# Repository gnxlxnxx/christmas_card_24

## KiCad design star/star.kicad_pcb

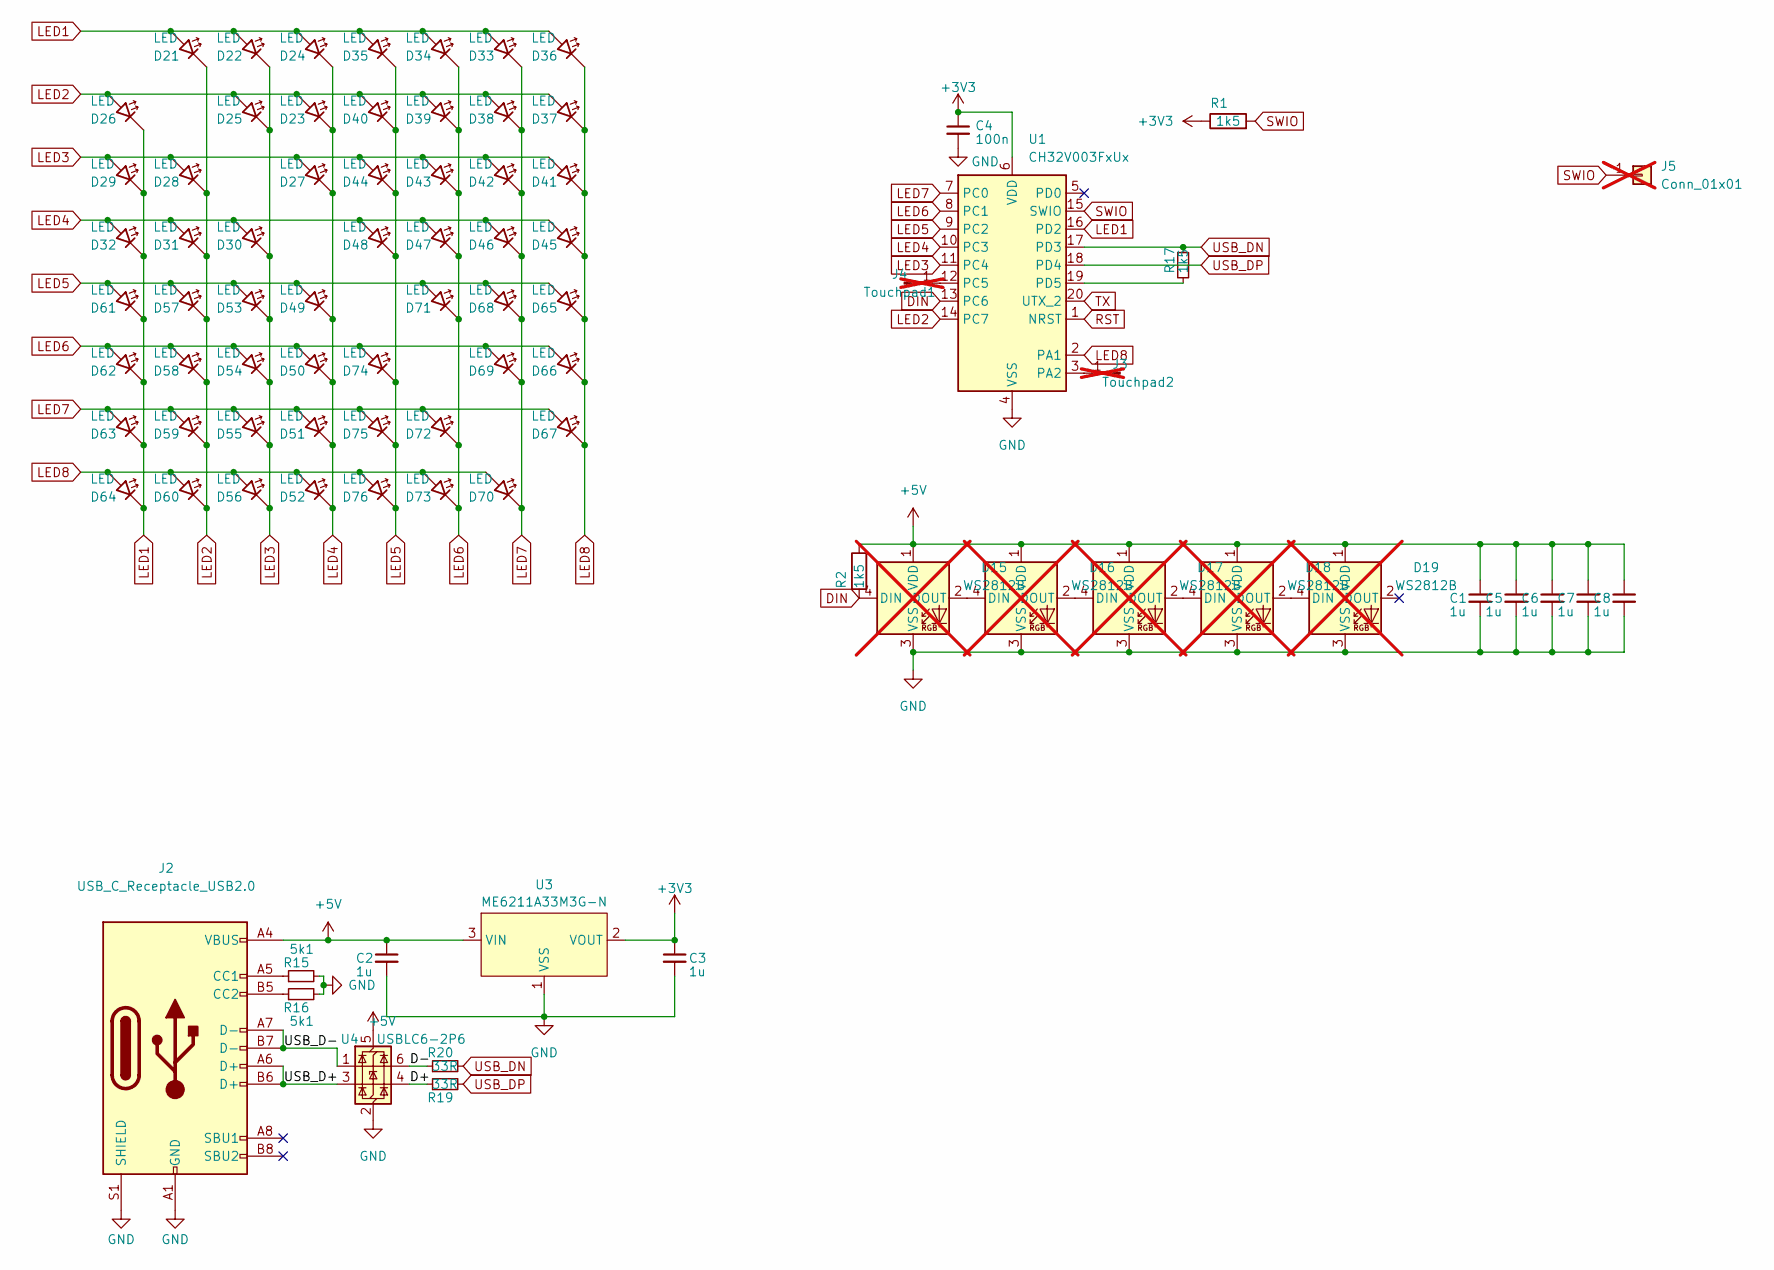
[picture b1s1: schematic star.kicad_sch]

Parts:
C1, C2, C3, C5, C6, C7, C8: 1u; C_0402_1005Metric; LCSC C52923
C4: 100n; C_0402_1005Metric; LCSC C1525
D15, D16, D17, D18, D19: WS2812B; LED_WS2812B_PLCC4_5.0x5.0mm_P3.2mm; LCSC C965555; not fitted
D21, D22, D23, D24, D25, D26, D27, D28, D29, D30, D31, D32, D33, D34, D35, D36, D37, D38, D39, D40, D41, D42, D43, D44, D45, D46, D47, D48, D49, D50, D51, D52, D53, D54, D55, D56, D57, D58, D59, D60, D61, D62, D63, D64, D65, D66, D67, D68, D69, D70, D71, D72, D73, D74, D75, D76: LED; LED_0603_1608Metric_Pad1.05x0.95mm_HandSolder; LCSC C497938
J2: USB_C_Receptacle_USB2.0; TYPE C 16 PIN MIDDLE MOUNT CH 0.52; LCSC C2927036
J3: Touchpad2; touch_pad; not fitted
J4: Touchpad1; touch_pad; not fitted
J5: Conn_01x01; pogo_pin_conn_01x01; not fitted
R1, R2, R17: 1k5; R_0402_1005Metric; LCSC C25867
R15, R16: 5k1; R_0402_1005Metric; LCSC C25905
R19, R20: 33R; R_0402_1005Metric; LCSC C25105
U1: CH32V003FxUx; QFN-20-1EP_3x3mm_P0.4mm_EP1.65x1.65mm; LCSC C5299908
U3: ME6211A33M3G-N; SOT-23-3; LCSC C168807
U4: USBLC6-2P6; SOT-666; LCSC C2827693

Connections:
+3V3: C3.1, C4.1, R1.1, U1.6 (VDD), U3.2 (VOUT)
+5V: C1.1, C2.1, C5.1, C6.1, C7.1, C8.1, D15.1 (VDD), D16.1 (VDD), D17.1 (VDD), D18.1 (VDD), D19.1 (VDD), J2.A4 (VBUS), J2.A9 (VBUS), J2.B4 (VBUS), J2.B9 (VBUS), R2.1, U3.3 (VIN), U4.5 (VBUS)
/D+: R19.1, U4.4 (I/O2)
/D-: R20.1, U4.6 (I/O1)
/USB_D+: J2.A6 (D+), J2.B6 (D+), U4.3 (I/O2)
/USB_D-: J2.A7 (D-), J2.B7 (D-), U4.1 (I/O1)
DIN: D15.4 (DIN), R2.2, U1.13 (PC6)
GND: C1.2, C2.2, C3.2, C4.2, C5.2, C6.2, C7.2, C8.2, D15.3 (VSS), D16.3 (VSS), D17.3 (VSS), D18.3 (VSS), D19.3 (VSS), J2.A1 (GND), J2.A12 (GND), J2.B1 (GND), J2.B12 (GND), J2.S1 (SHIELD), R15.2, R16.2, U1.4 (VSS), U1.21 (VSS), U3.1 (VSS), U4.2 (GND)
LED1: D21.2 (A), D22.2 (A), D24.2 (A), D26.1 (K), D29.1 (K), D32.1 (K), D33.2 (A), D34.2 (A), D35.2 (A), D36.2 (A), D61.1 (K), D62.1 (K), D63.1 (K), D64.1 (K), U1.16 (PD2)
LED2: D21.1 (K), D23.2 (A), D25.2 (A), D26.2 (A), D28.1 (K), D31.1 (K), D37.2 (A), D38.2 (A), D39.2 (A), D40.2 (A), D57.1 (K), D58.1 (K), D59.1 (K), D60.1 (K), U1.14 (PC7)
LED3: D22.1 (K), D25.1 (K), D27.2 (A), D28.2 (A), D29.2 (A), D30.1 (K), D41.2 (A), D42.2 (A), D43.2 (A), D44.2 (A), D53.1 (K), D54.1 (K), D55.1 (K), D56.1 (K), U1.11 (PC4)
LED4: D23.1 (K), D24.1 (K), D27.1 (K), D30.2 (A), D31.2 (A), D32.2 (A), D45.2 (A), D46.2 (A), D47.2 (A), D48.2 (A), D49.1 (K), D50.1 (K), D51.1 (K), D52.1 (K), U1.10 (PC3)
LED5: D35.1 (K), D40.1 (K), D44.1 (K), D48.1 (K), D49.2 (A), D53.2 (A), D57.2 (A), D61.2 (A), D65.2 (A), D68.2 (A), D71.2 (A), D74.1 (K), D75.1 (K), D76.1 (K), U1.9 (PC2)
LED6: D34.1 (K), D39.1 (K), D43.1 (K), D47.1 (K), D50.2 (A), D54.2 (A), D58.2 (A), D62.2 (A), D66.2 (A), D69.2 (A), D71.1 (K), D72.1 (K), D73.1 (K), D74.2 (A), U1.8 (PC1)
LED7: D33.1 (K), D38.1 (K), D42.1 (K), D46.1 (K), D51.2 (A), D55.2 (A), D59.2 (A), D63.2 (A), D67.2 (A), D68.1 (K), D69.1 (K), D70.1 (K), D72.2 (A), D75.2 (A), U1.7 (PC0)
LED8: D36.1 (K), D37.1 (K), D41.1 (K), D45.1 (K), D52.2 (A), D56.2 (A), D60.2 (A), D64.2 (A), D65.1 (K), D66.1 (K), D67.1 (K), D70.2 (A), D73.2 (A), D76.2 (A), U1.2 (PA1)
unnamed: D15.2 (DOUT), D16.4 (DIN)
unnamed: D16.2 (DOUT), D17.4 (DIN)
unnamed: D17.2 (DOUT), D18.4 (DIN)
unnamed: D18.2 (DOUT), D19.4 (DIN)
unnamed: J2.A5 (CC1), R15.1
unnamed: J2.B5 (CC2), R16.1
unnamed: J3.1, U1.3 (PA2)
unnamed: J4.1, U1.12 (PC5)
unnamed: R17.2, U1.19 (PD5)
RST: U1.1 (NRST)
SWIO: J5.1, R1.2, U1.15 (SWIO)
TX: U1.20 (UTX_2)
USB_DN: R17.1, R20.2, U1.17 (PD3)
USB_DP: R19.2, U1.18 (PD4)

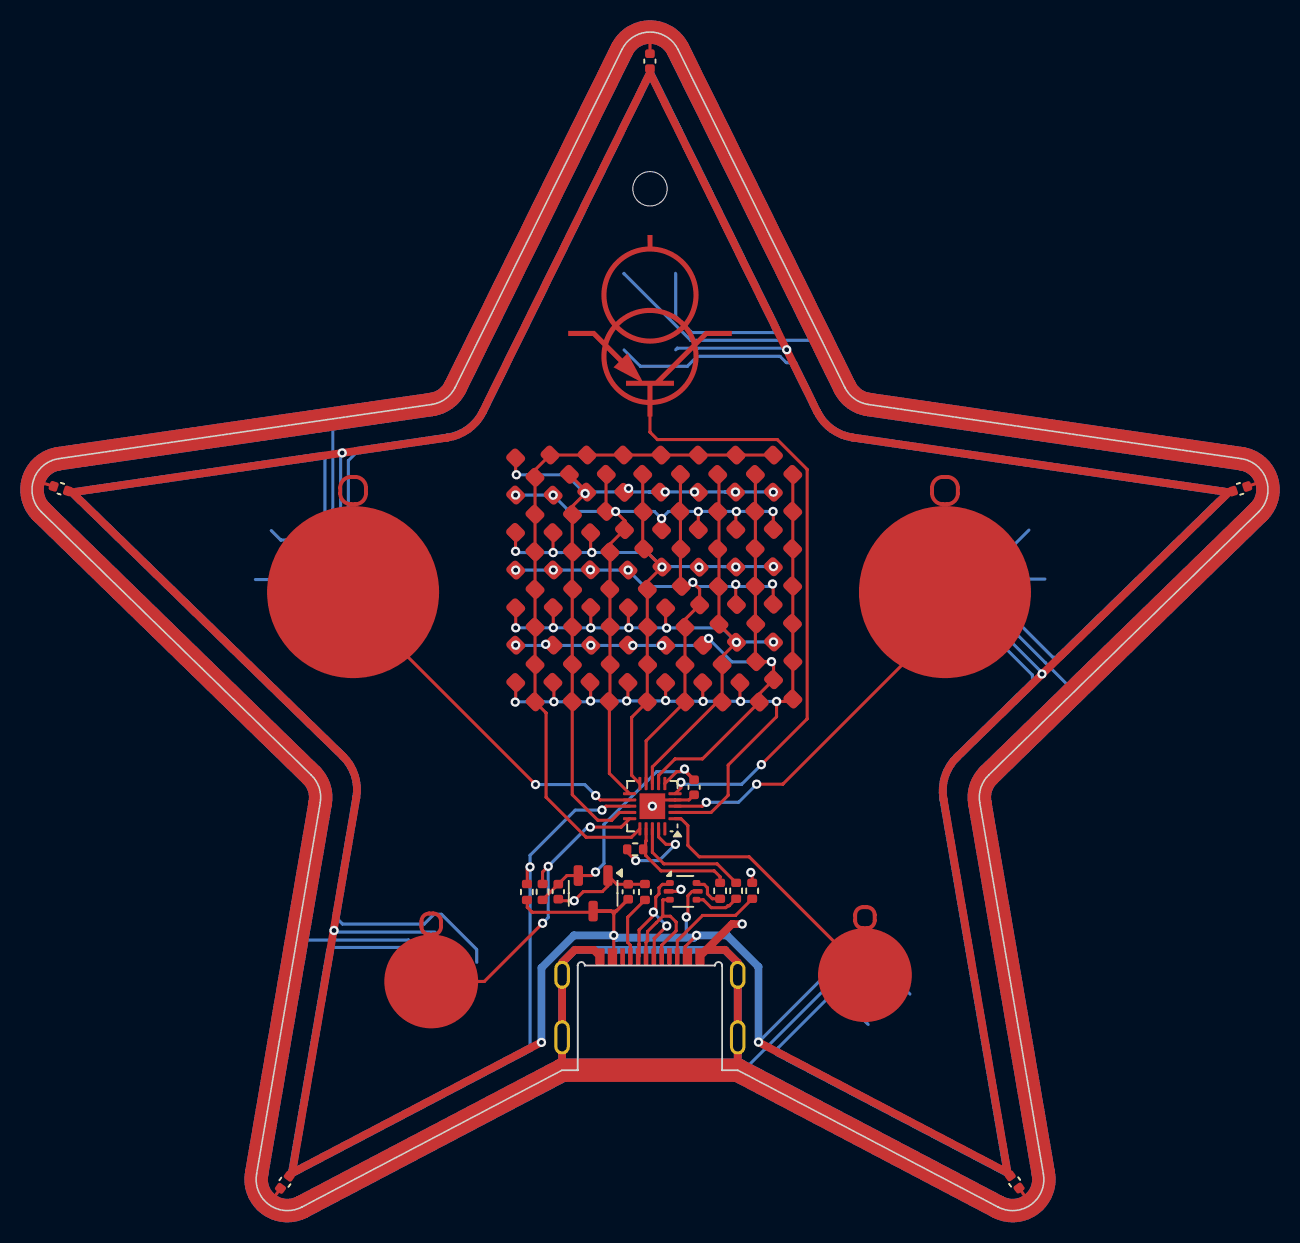
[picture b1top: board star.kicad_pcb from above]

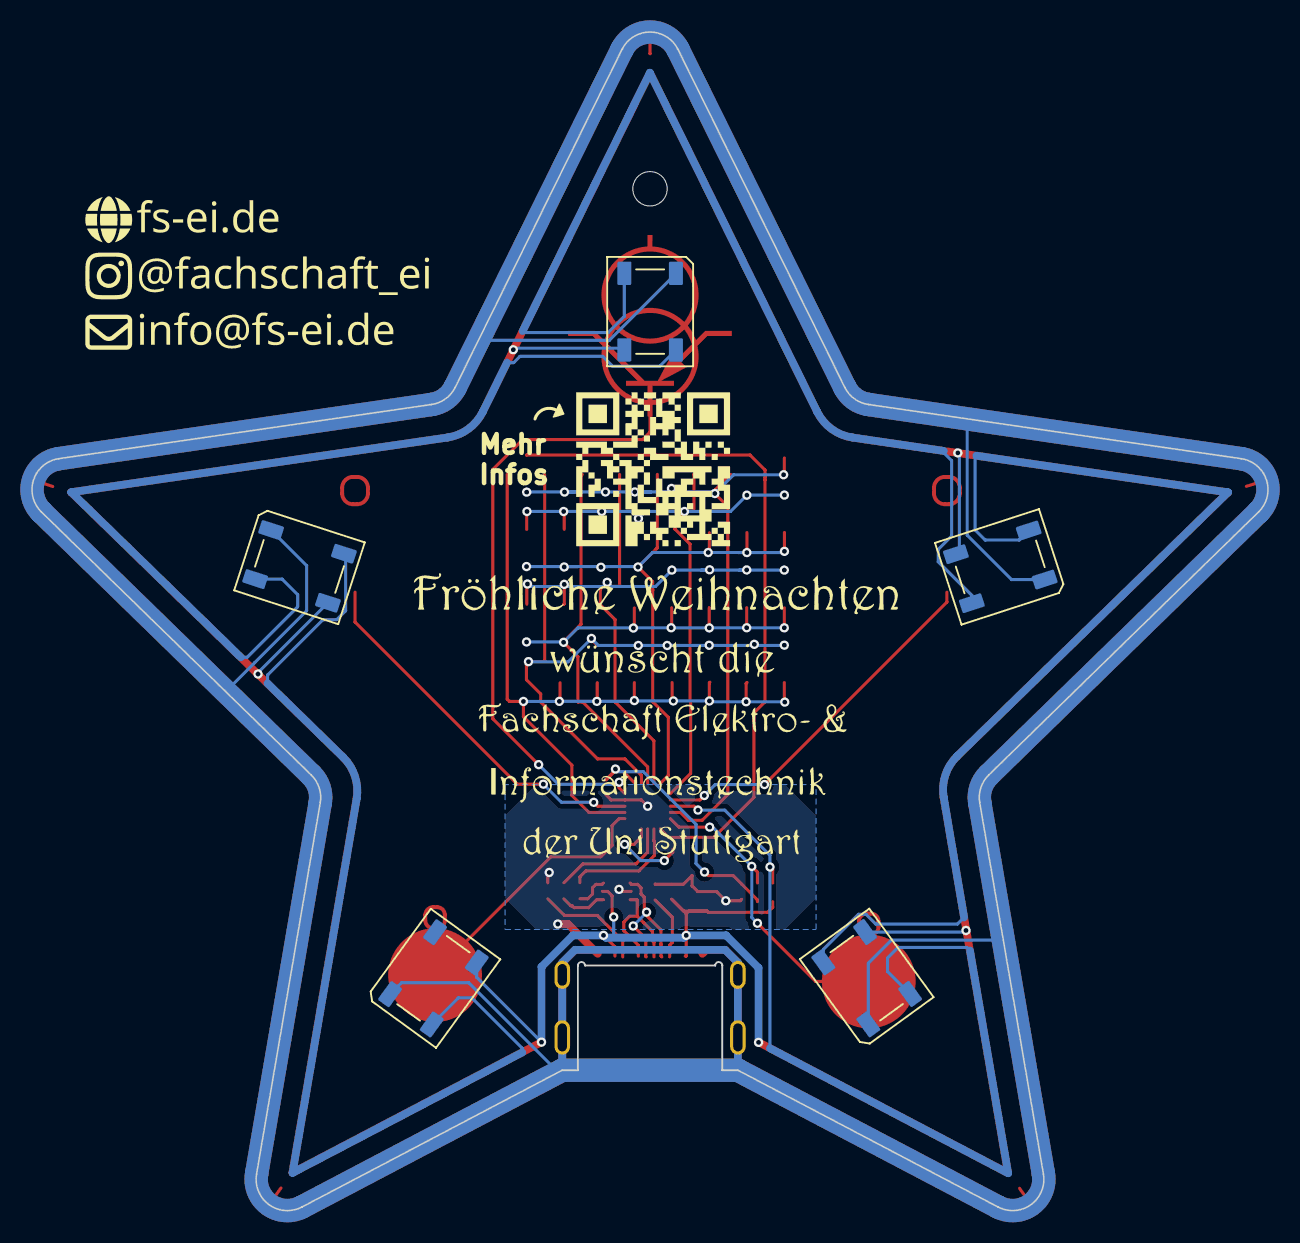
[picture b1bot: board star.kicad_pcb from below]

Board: 2 copper layers, 79.1 x 75.4 mm, 82 parts (5 on the bottom side), 28 nets.

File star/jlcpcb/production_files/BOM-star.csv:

Comment,Designator,Footprint,LCSC,Quantity
100n,C4,C_0402_1005Metric,C1525,1
ME6211A33M3G-N,U3,SOT-23-3,C168807,1
33R,"R19,R20",R_0402_1005Metric,C25105,2
1k5,"R1,R17,R2",R_0402_1005Metric,C25867,3
5k1,"R15,R16",R_0402_1005Metric,C25905,2
USBLC6-2P6,U4,SOT-666,C2827693,1
USB_C_Receptacle_USB2.0,J2,TYPE C 16 PIN MIDDLE MOUNT CH 0.52,C2927036,1
LED,"D21,D22,D23,D24,D25,D26,D27,D28,D29,D30,D31,D32,D33,D34,D35,D36,D37,D38,D39,D40,D41,D42,D43,D44,D45,D46,D47,D48,D49,D50,D51,D52,D53,D54,D55,D56,D57,D58,D59,D60,D61,D62,D63,D64,D65,D66,D67,D68,D69,D70,D71,D72,D73,D74,D75,D76",LED_0603_1608Metric_Pad1.05x0.95mm_HandSolder,C497938,56
1u,"C1,C2,C3,C5,C6,C7,C8",C_0402_1005Metric,C52923,7
CH32V003FxUx,U1,QFN-20-1EP_3x3mm_P0.4mm_EP1.65x1.65mm,C5299908,1
WS2812B,"D16,D18",LED_WS2812B_PLCC4_5.0x5.0mm_P3.2mm,C965555,2

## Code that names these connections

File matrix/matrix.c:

#include <ch32fun.h>
#include <stdint.h>
#include "matrix.h"

#include "gamma_lut.h"

/// LED1:   PD2 *
/// LED2:   PC7 *
/// LED3:   PC4 *
/// LED4:   PC3 *
/// LED5:   PC2 *
/// LED6:   PC1 *
/// LED7:   PC0 *
/// LED8:   PA1 *
///
/// TIM2:
/// 00:     PD4  PD3  PC0  PD7
/// 01:     PC5  PC2* PD2* PC1* *
/// 10:     PC1  PD3  PC0  PD7 
/// 11:     PC1  PC7  PD6  PD5 
///
/// TIM1:
/// 00:     PD2 /PD0  PA1*/PA2  PC3*/PD1  PC4* *
/// 01:     PC6 /PC3  PC7*/PC4  PC0*/PD1  PD3  *
/// 11:     PC4 /PC3  PC7 /PD2  PC5 /PC6  PD4


#define PWM_MAX 4096

#define ROWCOUNT (MATRIX_WIDTH)
#define GROUPCOUNT 2

#define G0T0C2_COL 1
#define G0T0C3_COL 6
#define G0T1C2_COL 4
#define G0T1C3_COL 0
#define G0T1C4_COL 5
#define G1T0C2_COL 7
#define G1T0C3_COL 3
#define G1T0C4_COL 2

uint8_t matrix_data[MATRIX_HEIGHT][MATRIX_WIDTH] = {0};

static uint8_t row = 0, group = 0;

static const struct row {
  GPIO_TypeDef *port;
  uint8_t pin;
  uint8_t group;
} rows[ROWCOUNT] = {
  { GPIOD, 2, 0 },
  { GPIOC, 7, 0 },
  { GPIOC, 4, 1 },
  { GPIOC, 3, 1 },
  { GPIOC, 2, 0 },
  { GPIOC, 1, 0 },
  { GPIOC, 0, 0 },
  { GPIOA, 1, 1 },
};

static void float_all(void) {
  // for (int i = 0; i < ROWCOUNT; i++) {
  //   rows[i].port->CFGLR = (rows[i].port->CFGLR & ~(0xf<<(4*rows[i].pin)))
  //     | GPIO_CNF_IN_FLOATING<<(4*rows[i].pin);
  // }
  rows[0].port->CFGLR = (rows[0].port->CFGLR & ~(0xf<<(4*rows[0].pin)))
    | GPIO_CNF_IN_FLOATING<<(4*rows[0].pin);
  GPIOC->CFGLR = (GPIOC->CFGLR & ~0xf00fffff) | 0x40044444;
  rows[7].port->CFGLR = (rows[7].port->CFGLR & ~(0xf<<(4*rows[7].pin)))
    | GPIO_CNF_IN_FLOATING<<(4*rows[7].pin);
}

static void attach_group(uint8_t group, uint8_t row) {
  // for (int i = 0; i < ROWCOUNT; i++) {
  //   if (i != row && rows[i].group == group) {
  //     rows[i].port->CFGLR = (rows[i].port->CFGLR & ~(0xf<<(4*rows[i].pin)))
  //       | (GPIO_Speed_10MHz | GPIO_CNF_OUT_OD_AF)<<(4*rows[i].pin);
  //   }
  // }
  switch(group) {
    case 0:
      rows[0].port->CFGLR = (rows[0].port->CFGLR & ~(0xf<<(4*rows[0].pin)))
        | (GPIO_Speed_10MHz | GPIO_CNF_OUT_OD_AF)<<(4*rows[0].pin);
      GPIOC->CFGLR = (GPIOC->CFGLR & ~0xf0000fff) | 0xd0000ddd;
      break;
    case 1:
      GPIOC->CFGLR = (GPIOC->CFGLR & ~0xff000) | 0xdd000;
      rows[7].port->CFGLR = (rows[7].port->CFGLR & ~(0xf<<(4*rows[7].pin)))
        | (GPIO_Speed_10MHz | GPIO_CNF_OUT_OD_AF)<<(4*rows[7].pin);
      break;
  }

}

static void set_high(uint8_t row) {
  rows[row].port->CFGLR = (rows[row].port->CFGLR & ~(0xf<<(4*rows[row].pin)))
    | (GPIO_Speed_10MHz | GPIO_CNF_OUT_PP)<<(4*rows[row].pin);
}

static uint16_t get_val(uint8_t row, uint8_t col) {
  return gamma_lut[matrix_data[(row <= col) ? row : row - 1][col]];
}

void matrix_init(void) {
  RCC->APB2PRSTR |= RCC_APB2Periph_TIM1;
  RCC->APB2PRSTR &= ~(RCC_APB2Periph_TIM1);
  RCC->APB1PRSTR |= RCC_APB1Periph_TIM2;
  RCC->APB1PRSTR &= ~(RCC_APB1Periph_TIM2);

  TIM1->ATRLR = PWM_MAX;
  TIM2->ATRLR = PWM_MAX;

  TIM1->SWEVGR |= TIM_UG;
  TIM2->SWEVGR |= TIM_UG;

  TIM1->CTLR1 |= TIM_ARPE;
  TIM2->CTLR1 |= TIM_ARPE;

  TIM1->CTLR1 |= TIM_CEN;
  TIM2->CTLR1 |= TIM_CEN;

  TIM1->BDTR |= TIM_MOE;
  TIM2->BDTR |= TIM_MOE;

  TIM1->CHCTLR1 |= TIM_OCMode_PWM1 | TIM_OCMode_PWM1<<8;
  TIM1->CHCTLR2 |= TIM_OCMode_PWM1 | TIM_OCMode_PWM1<<8;
  TIM2->CHCTLR1 |= TIM_OCMode_PWM1 | TIM_OCMode_PWM1<<8;
  TIM2->CHCTLR2 |= TIM_OCMode_PWM1 | TIM_OCMode_PWM1<<8;

  // for (int i = 0; i < ROWCOUNT; i++ ) {
  //   rows[i].port->OUTDR |= 1<<rows[i].pin;
  // }
  rows[0].port->OUTDR |= 1<<rows[0].pin;
  GPIOC->OUTDR |= 0b10011111;
  rows[7].port->OUTDR |= 1<<rows[7].pin;
}

void matrix_update(void) {
  float_all();

  group++;
  if (group >= GROUPCOUNT) {
    group = 0;
    row = (row + 1) % ROWCOUNT;
  }

  switch (group) {
    case 0:
      AFIO->PCFR1 = (AFIO->PCFR1 & ~(AFIO_PCFR1_TIM1_REMAP | AFIO_PCFR1_TIM2_REMAP))
        | AFIO_PCFR1_TIM1_REMAP_PARTIALREMAP1 | AFIO_PCFR1_TIM2_REMAP_PARTIALREMAP1;
      TIM1->CCER = TIM_CC2E | TIM_CC2P | TIM_CC3E | TIM_CC3P;
      TIM2->CCER = TIM_CC2E | TIM_CC2P | TIM_CC3E | TIM_CC3P | TIM_CC4E | TIM_CC4P;

      TIM1->CH2CVR = get_val(row, G0T0C2_COL);
      TIM1->CH3CVR = get_val(row, G0T0C3_COL);
      TIM2->CH2CVR = get_val(row, G0T1C2_COL);
      TIM2->CH3CVR = get_val(row, G0T1C3_COL);
      TIM2->CH4CVR = get_val(row, G0T1C4_COL);

      attach_group(group, row);
      break;
    case 1:
      AFIO->PCFR1 = (AFIO->PCFR1 & ~AFIO_PCFR1_TIM1_REMAP) | AFIO_PCFR1_TIM1_REMAP_NOREMAP;
      TIM1->CCER = TIM_CC2E | TIM_CC2P | TIM_CC3E | TIM_CC3P | TIM_CC4E | TIM_CC4P;

      if (row < ROWCOUNT - 1) {
        TIM1->CH2CVR = get_val(row, G1T0C2_COL);
      }
      TIM1->CH3CVR = get_val(row, G1T0C3_COL);
      TIM1->CH4CVR = get_val(row, G1T0C4_COL);

      attach_group(group, row);
      break;
  }

  TIM1->CNT = 0;
  TIM2->CNT = 0;
  set_high(row);
}

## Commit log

2023-12-01 Add WS2812 output
2023-12-01 Add submodule for toolchain
2023-12-14 initial (mostly working) state
    only the touch pads are completely missing
2023-12-14 add touch pfush
2023-12-14 fix order
2023-12-15 add basic timer stuff (TIM1 doesn't seem to work)
2023-12-15 add change_col function
2023-12-15 fix touch pad & cleanup
2023-12-15 fix makefile
2023-12-15 remove unused stuff
2023-12-15 add matrix output
2023-12-15 Improve main structure
2023-12-15 left key and right key input on touch, for presentations
2023-12-15 swtich button order
2023-12-15 add animation on button press (hacky)
2023-12-15 animate a bit better
2023-12-15 multiplex faster
2023-12-15 improve multiplex output
    works now after fixing rv003usb
2023-12-15 Add .gitignore
2023-12-16 Workaround hw bug
2023-12-16 Allow automatic opening of website
2023-12-16 Use less magic numbers in usb_config
2023-12-16 Update matrix.c
    Make column 3 usable (probably reminisce of debugging)
2023-12-16 Mode switching and random (inverted) pulse mode
2023-12-17 Add ws2812 snow mode
2023-12-17 Add 2nd url macro for Windows
2023-12-17 decrease brightness of adjecent leds for button effect
2023-12-17 reduce speed of front matrix effect
2023-12-17 Delay col change so leds are all off
2023-12-17 Remove unneeded and invalid command
2023-12-17 Add gamepad control
2023-12-17 Map both buttons onto one axis
2023-12-17 Improve scale when both buttons pressed
2023-12-17 small cleanup
2023-12-17 Lock animations if both keys are pressed at start
2023-12-18 Implement snow ball with hue shift and ws2812 fading
2023-12-18 Format main.c
2023-12-18 Add snowfall animation on front
2023-12-18 Add sparkle animation to front
2023-12-18 Add huewheel animation to back
2023-12-18 Slow down sparkle effect
2023-12-18 Removo unused variables and functions
2023-12-18 Use less magic numbers in usb_config.h
2023-12-18 Fix usb not working under windows
2023-12-18 Revert "Use less magic numbers in usb_config.h"
    This reverts commit f4e10f9ef5b4aadc140d87c00fd637788a4d668c.
2023-12-18 Allow usage of www button
2023-12-28 Update rv003usb to fixed version
2024-12-16 Update submodules
2024-12-16 Fix pins being renamed
2024-12-16 add charlieplexing
2024-12-16 Remove 6th WLED (partially)
2024-12-16 Improve usb stack
2024-12-17 Break everything
2024-12-17 Fix some stuff
2024-12-17 Make buttons work
2024-12-17 Some small cleanup
2024-12-17 Add animated writing on the charlieplexed matrix
2024-12-17 Use buttons
2024-12-17 Adapt ws2812 to new LED arrangement
2024-12-17 Move stuff to matrix file to make stuff prettier
2024-12-17 Add preliminary snowfall animation
2024-12-18 Start attempting pwm implementation
2024-12-18 Broken pwm
2024-12-18 Should go to sleep
2024-12-18 There is hope!
2024-12-18 It fucking works! Nice.
2024-12-18 Cleanup
2024-12-18 Fix warnings
2024-12-18 Add additional modes
    mostly just copies of last years modes
2024-12-18 Make different glich that is less annoying
2024-12-18 Increase probability of Snowflake
2024-12-18 Remove consecutive snowflakes
2024-12-18 Move matrix stuff to own directory
2024-12-18 Improve scrolling text
2024-12-18 Make font proportional
2024-12-18 Geile Übergänge :D
2024-12-18 Modularize and improve text
2024-12-18 Improve animations
2024-12-19 Snake
2024-12-19 Speed things up
2024-12-19 Divergent scroll speeds for logo vs text
2024-12-19 add PCB files
2025-08-26 Update rv003usb
2025-08-26 Fix some smaller issues from after final version
2025-08-26 Optimize matrix
2025-08-26 Improve snake
2025-11-18 Work towards xmas card 25
2025-11-18 Add swio pin check
2025-12-18 Remove unused variable
2025-12-18 Modify ws2812 code for new card
2025-12-18 Fix out of bounds read
